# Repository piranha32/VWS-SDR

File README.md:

# Vienna Wireless Society Software Defined Receiver (VWS-SDR)
Compact breadboard module version of the VWS SDR frontend. 

Changes compared to the source design:
- Removed clock generator and controller modules. This module implements only downconversion and filtering.
- Added pin header for installation on a breadboard.
- Added 3.3V regulator to provide voltage used by the multiplexer chip. The voltage is also available on the pin header, and can be used to power the clock generator module.
- Replaced electrolytic capacitors with SMD versions.
- All remaining passives use 0603 footprints.

# Original description

This repository contains the files for a 2025 project by the [Vienna Wireless Society's](https://viennawireless.net/wp/) Makers Group. This project aims to build the RF front end of a software defined receiver covering the HF bands. The goals of the project are: 

1. Learn how to use KiCAD, and 
2. Learn surface mount assembly techniques. 

The VWS-SDR design draws heavily from the RF board of the T41-EP Software Defined Transceiver (SDT) originally designed by Al Peter-AC8GY and Jack Purdum-W8TEE. The T41-EP is a self-contain SDT that does not require an external PC, laptop, or tablet to use. Al and Jack wrote a book, available on [Amazon](https://www.amazon.com/dp/B0D25FV48C), describing the theory and operation of the T41-EP.

## Design overview 

The VWS-SDR has stages shown in the block diagram below.

1. A gain stage based on the [GALI-S66+](https://www.minicircuits.com/WebStore/dashboard.html?model=GALI-S66%2B) MMIC amplifier.
2. A [Tayloe Mixer](http://norcalqrp.org/files/Tayloe_mixer_x3a.pdf) that uses quadrature signals generated by a [Si5351](https://www.digikey.com/en/htmldatasheets/production/1316951/0/0/1/si535x-tmstk) clock generator and a [74CBTLV3253](https://www.ti.com/product/SN74CBTLV3253) 2-channel analog multiplexer to mix the RF signals to IF.
3. An anti-aliasing low-pass filter followed by a USB soundcard to digitize the IF signal.
4. Demodulation will be performed in software using [quisk](http://james.ahlstrom.name/quisk/).

## Instructions

Download this repository to your computer. Open the `KiCad\VWS-SDR-ref-design.kicad_pro` file using the [KiCad](https://www.kicad.org/) EDA software package. This repository includes a few custom symbols and footprints which should automatically be added to your library lists by KiCad.

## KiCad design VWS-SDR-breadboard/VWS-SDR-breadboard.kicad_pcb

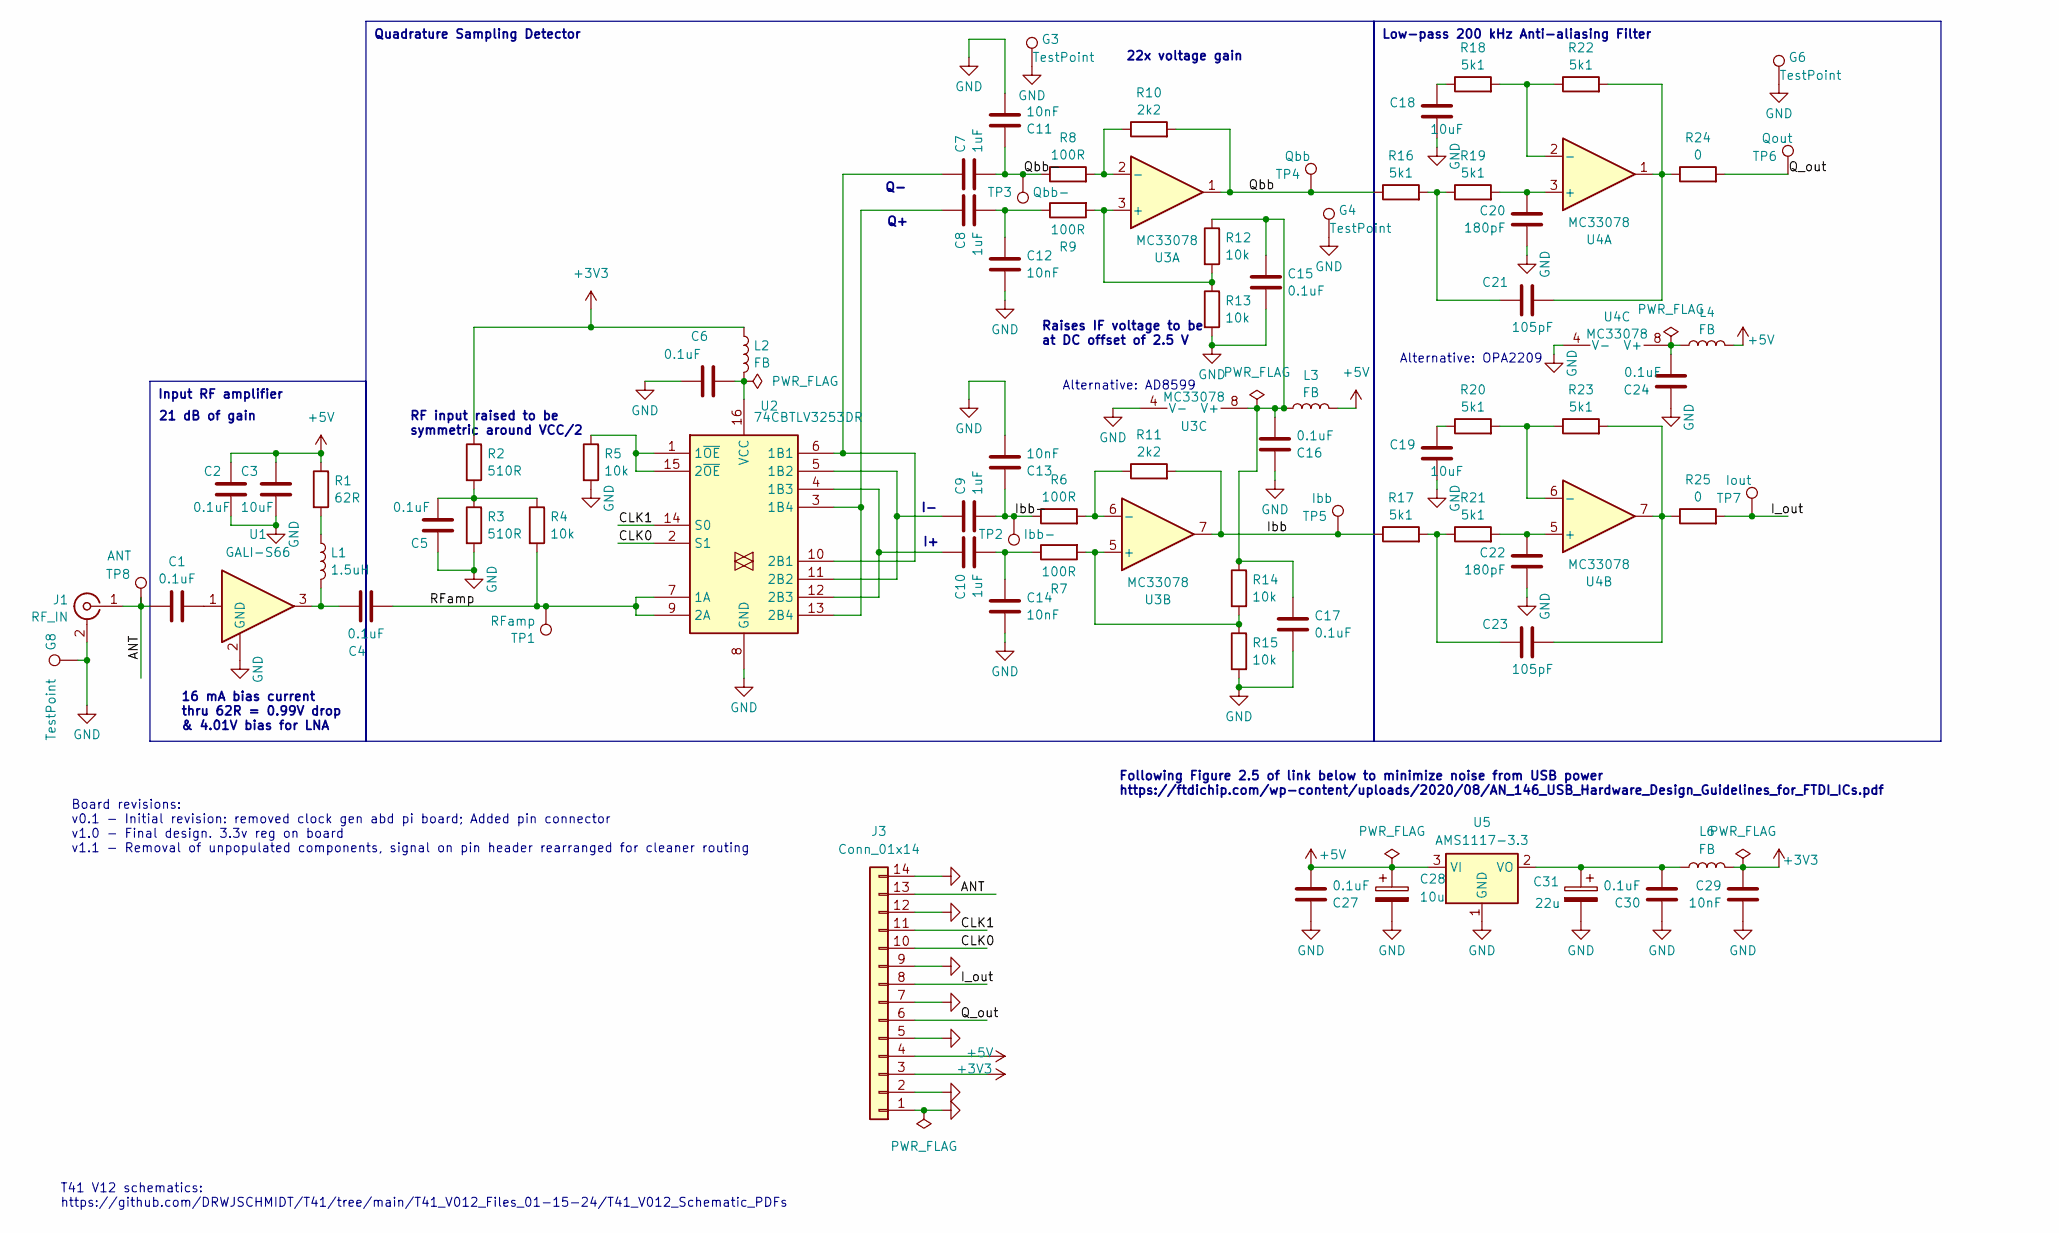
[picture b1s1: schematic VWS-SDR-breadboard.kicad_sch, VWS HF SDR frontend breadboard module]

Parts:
C1, C2, C4, C5, C6, C15, C16, C17, C24, C27, C30: 0.1uF; C_0603_1608Metric; Mouser Part Number C1206C104K5RACTU
C3, C18, C19: 10uF; C_0603_1608Metric; Mouser Part Number 80-C1206C106K4P
C7, C8, C9, C10: 1uF; C_0603_1608Metric; Mouser Part Number 187-CL31B105KBHNNNE
C11, C12, C13, C14, C29: 10nF; C_0603_1608Metric; Mouser Part Number 80-C1206C103K5R7210
C20, C22: 180pF; C_0603_1608Metric; Mouser Part Number 791-1206B181K160CT
C21, C23: 105pF; C_0603_1608Metric; Mouser Part Number 581-12065C101KAT2A
C28: 10u; CP_Elec_6.3x5.9; Mouser Part Number 80-ESK475M016AC3AA
C31: 22u; CP_Elec_6.3x5.9; Mouser Part Number 80-ESK475M016AC3AA
G3, G4, G6, G8: TestPoint; TestPoint_Pad_D2.0mm
J1: RF_IN; SMA_Amphenol_132134-11_Vertical; Mouser Part Number 712-CONSMA001-G
J3: Conn_01x14; PinHeader_1x14_P2.54mm_Vertical
L1: 1.5uH; R_0603_1608Metric; Mouser Part Number 81-LQM31PN1R5M00L
L2, L3, L4, L6: FB; R_0603_1608Metric; Mouser Part Number 875-HZ1206E601R-10
R1: 62R; R_0603_1608Metric; Mouser Part Number 652-CR1206FX-62R0ELF
R2, R3: 510R; R_0603_1608Metric; Mouser Part Number 652-CR1206FX-5100ELF
R4, R5, R12, R13, R14, R15: 10k; R_0603_1608Metric; Mouser Part Number 652-CR1206FX-1002ELF
R6, R7, R8, R9: 100R; R_0603_1608Metric; Mouser Part Number 652-CR1206FX-1000ELF
R10, R11: 2k2; R_0603_1608Metric; Mouser Part Number 652-CR1206FX-2201ELF
R16, R17, R18, R19, R20, R21, R22, R23: 5k1; R_0603_1608Metric; Mouser Part Number 652-CR1206JW-512ELF
R24, R25: 0; R_0603_1608Metric; Mouser Part Number 71-CRCW12060000Z0EAC
TP1: RFamp; TestPoint_Pad_D2.0mm
TP2: Ibb-; TestPoint_Pad_D2.0mm
TP3: Qbb-; TestPoint_Pad_D2.0mm
TP4: Qbb; TestPoint_Pad_D2.0mm
TP5: Ibb; TestPoint_Pad_D2.0mm
TP6: Qout; TestPoint_Pad_D2.0mm
TP7: Iout; TestPoint_Pad_D2.0mm
TP8: ANT; TestPoint_Pad_D2.0mm
U1: GALI-S66; SOT-89-3; Mouser Part Number 139-GALI-S66
U2: 74CBTLV3253DR; SOIC-16_3.9x9.9mm_P1.27mm; Mouser Part Number 595-SN74CBTLV3253DR
U3, U4: MC33078; SOIC-8_3.9x4.9mm_P1.27mm; Mouser Part Number 595-MC33078DR
U5: AMS1117-3.3; SOT-223-3_TabPin2

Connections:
+3V3: C29.2, J3.3, L2.1, L6.1, R2.1
+5V: C2.2, C3.2, C27.1, C28.1, J3.4, L3.2, L4.2, R1.1, U5.3 (VI)
/ANT: C1.1, J1.1 (In), J3.13, TP8.1
/CLK0: J3.10, U2.2 (S1)
/CLK1: J3.11, U2.14 (S0)
/I_out: J3.8, R25.2, TP7.1
/Ibb: R11.2, R17.1, TP5.1, U3.7
/Ibb-: C9.1, C13.2, R6.1, TP2.1
/Q_out: J3.6, R24.2, TP6.1
/Qbb: R10.2, R16.1, TP4.1, U3.1
/Qbb-: C7.1, C11.2, R8.1, TP3.1
/RFamp: C4.2, R4.2, TP1.1, U2.7 (1A), U2.9 (2A)
GND: C2.1, C3.1, C5.1, C6.1, C11.1, C12.1, C13.1, C14.1, C15.1, C16.2, C17.1, C18.1, C19.1, C20.1, C22.1, C24.2, C27.2, C28.2, C29.1, C30.2, C31.2, G3.1, G4.1, G6.1, G8.1, J1.2 (Ext), J3.1, J3.2, J3.5, J3.7, J3.9, J3.12, J3.14, R3.2, R5.2, R13.2, R15.2, U1.2 (GND), U2.8 (GND), U3.4 (V-), U4.4 (V-), U5.1 (GND)
unnamed: C1.2, U1.1
unnamed: C4.1, L1.2, U1.3
unnamed: C5.2, R2.2, R3.1, R4.1
unnamed: C10.1, C14.2, R7.1
unnamed: C8.1, C12.2, R9.1
unnamed: C18.2, R18.1
unnamed: C19.2, R20.1
unnamed: C21.1, R22.2, R24.1, U4.1
unnamed: C21.2, R16.2, R19.1
unnamed: C23.1, R23.2, R25.1, U4.7
unnamed: C23.2, R17.2, R21.1
unnamed: L1.1, R1.2
unnamed: C7.2, U2.6 (1B1), U2.10 (2B1)
unnamed: C9.2, U2.5 (1B2), U2.11 (2B2)
unnamed: C10.2, U2.4 (1B3), U2.12 (2B3)
unnamed: C8.2, U2.3 (1B4), U2.13 (2B4)
unnamed: R5.1, U2.1 (1~OE), U2.15 (2~OE)
unnamed: C6.2, L2.2, U2.16 (VCC)
unnamed: R9.2, R12.2, R13.1, U3.3 (+)
unnamed: R8.2, R10.1, U3.2 (-)
unnamed: R7.2, R14.2, R15.1, U3.5 (+)
unnamed: R6.2, R11.1, U3.6 (-)
unnamed: C15.2, C16.1, C17.2, L3.1, R12.1, R14.1, U3.8 (V+)
unnamed: C20.2, R19.2, U4.3 (+)
unnamed: R18.2, R22.1, U4.2 (-)
unnamed: C22.2, R21.2, U4.5 (+)
unnamed: R20.2, R23.1, U4.6 (-)
unnamed: C24.1, L4.1, U4.8 (V+)
unnamed: C30.1, C31.1, L6.2, U5.2 (VO)

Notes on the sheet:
Low-pass 200 kHz Anti-aliasing Filter
Quadrature Sampling Detector
Input RF amplifier
Raises IF voltage to be at DC offset of 2.5 V
T41 V12 schematics: https://github.com/DRWJSCHMIDT/T41/tree/main/T41_V012_Files_01-15-24/T41_V012_Schematic_PDFs
Following Figure 2.5 of link below to minimize noise from USB power https://ftdichip.com/wp-content/uploads/2020/08/AN_146_USB_Hardware_Design_Guidelines_for_FTDI_ICs.pdf
Alternative: OPA2209
21 dB of gain
Board revisions: v0.1 - Initial revision: removed clock gen abd pi board; Added pin connector v1.0 - Final design. 3.3v reg on board v1.1 - Removal of unpopulated components, signal on pin header rearranged for cleaner routing
Alternative: AD8599
16 mA bias current thru 62R = 0.99V drop & 4.01V bias for LNA
22x voltage gain
RF input raised to be symmetric around VCC/2

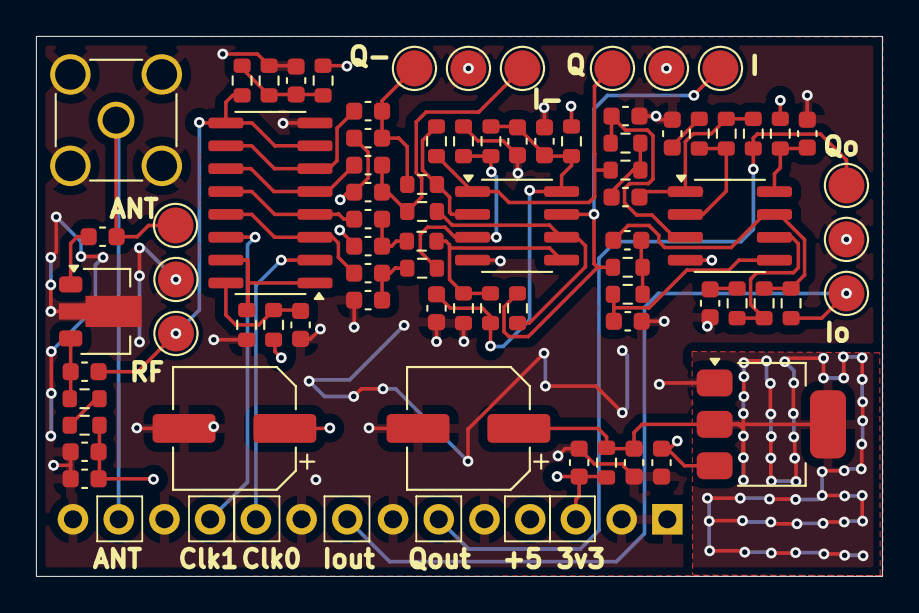
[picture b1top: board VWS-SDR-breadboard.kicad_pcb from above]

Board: 4 copper layers, 47.0 x 30.0 mm, 78 parts (1 on the bottom side), 42 nets.

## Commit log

2025-01-10 Cleaned up the schematic (removed unnecessary components), replaced R/C footprints with 0603, replaced testpoints wit smd footprints, made mounting holes smaller
2025-01-12 breadboard pcb v 1.0
2025-01-12 Board cleanup; Updated schematic info block
2025-01-12 Updated README; Added .gitignore
2025-01-12 v1.1: - Changed order of pins on the connector to simplify routing. I/Q should be closer to the power pins. clock should be closer to the antenna - Added GND fill on the Vcc layer under the antenna t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
2025-01-12 Added missing via to GND
